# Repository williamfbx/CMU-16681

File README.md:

# MRSD Project I
Subject Name: MRSD Project I  
Subject Code: 16681-A  
Semester Taken: Spring 2025  
Instructor: John M. Dolan  
Grade: A  
Difficulty: 5/5

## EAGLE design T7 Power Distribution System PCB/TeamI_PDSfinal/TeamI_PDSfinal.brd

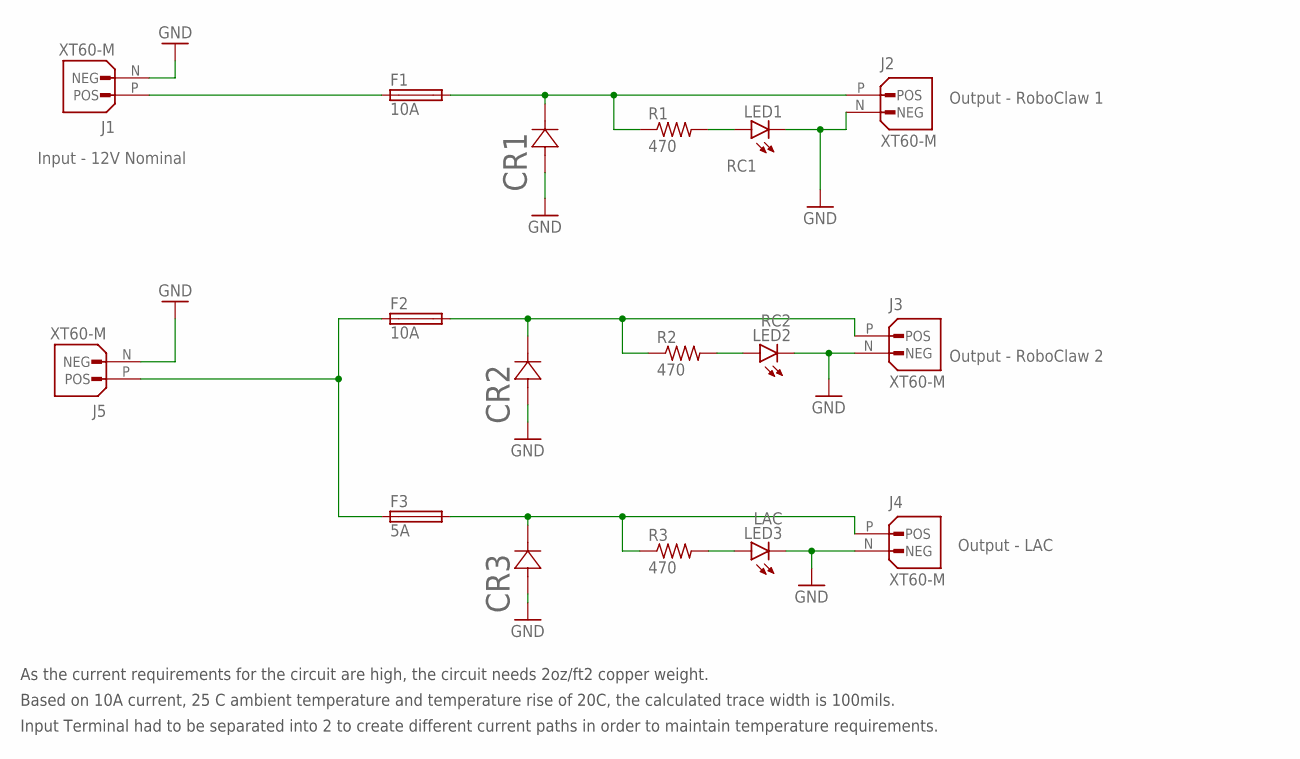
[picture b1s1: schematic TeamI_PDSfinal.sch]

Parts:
CR1, CR2, CR3: P4SMA16A; P4SMASERIES_LTF
F1, F2: 10A; TR5
F3: 5A; TE5
J1, J2, J3, J4, J5: XT60-M; AMASS_XT60-M
LED1: RC1; 1206
LED2: RC2; 1206
LED3: LAC; 1206
R1, R2, R3: 470; R1206

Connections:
GND: CR1.2, CR2.2, CR3.2, J1.N (NEG), J2.N (NEG), J3.N (NEG), J4.N (NEG), J5.N (NEG), LED1.C, LED2.C, LED3.C
unnamed: CR1.1, F1.2, J2.P (POS), R1.1
unnamed: CR3.1, F3.2, J4.P (POS), R3.1
unnamed: LED1.A, R1.2
unnamed: F1.1, J1.P (POS)
unnamed: CR2.1, F2.2, J3.P (POS), R2.1
unnamed: LED2.A, R2.2
unnamed: LED3.A, R3.2
unnamed: F2.1, F3.1, J5.P (POS)

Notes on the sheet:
Input - 12V Nominal
Output - RoboClaw 1
Output - RoboClaw 2
Output - LAC
As the current requirements for the circuit are high, the circuit needs 2oz/ft2 copper weight.
Based on 10A current, 25 C ambient temperature and temperature rise of 20C, the calculated trace width is 100mils.
Input Terminal had to be separated into 2 to create different current paths in order to maintain temperature requirements.

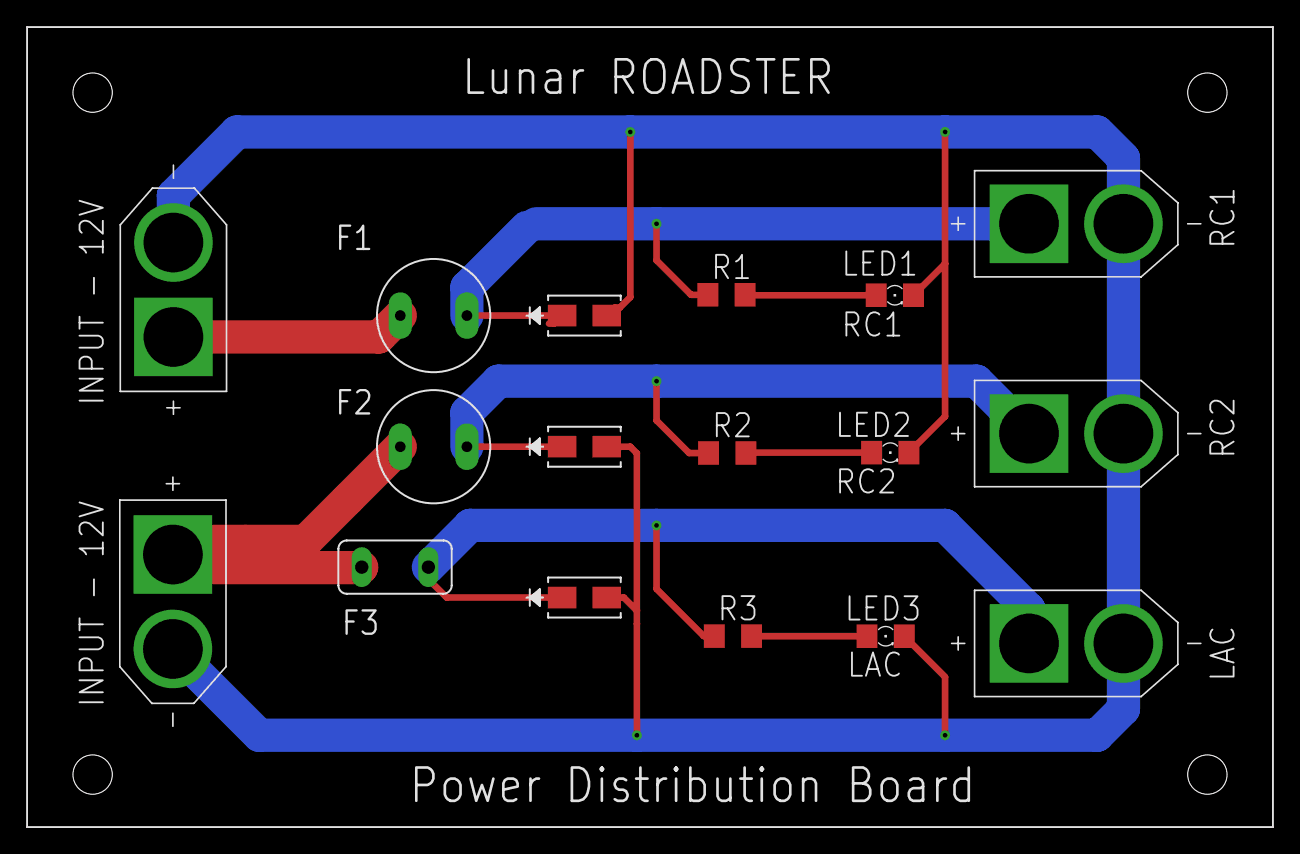
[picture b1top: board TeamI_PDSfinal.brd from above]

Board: 2 copper layers, 95.0 x 61.0 mm, 17 parts (0 on the bottom side), 9 nets.

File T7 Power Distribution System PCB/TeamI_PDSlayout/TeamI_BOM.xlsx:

Quantity | Value | Part Designator | Part Number | Vendor Link | Cost per part ($) | Package | Description
4 | P4SMA16A | CR1, CR2, CR3 | P4SMA16A | P4SMA16A | 0.43 | SMASERIES_LTF | Diode
6 | 10A | F1, F2 | TR5 - 37321000000 | 37321000000 | 1.29 | TE5 | Fuse
3 | 5A | F3 | TE5 - 39515000440 | 39515000440 | 1.57 | TE5 | Fuse
6 | XT60-M | J1, J2, J3, J4, J5 | XT60-M | XT60 | 0.89 | AMASS_XT60-M | Connector
5 | LEDSMT1206 | LED1, LED2, LED3 | 1206 SMD | 1206 SMD | 0.04 | 1206 | LED
5 | 470 Ω | R1, R2, R3 | CR1206-FX-4700ELF | CR1206-FX-4700ELF | 0.1 | R1206 | Resistor
 |  |  |  |  |  | 0

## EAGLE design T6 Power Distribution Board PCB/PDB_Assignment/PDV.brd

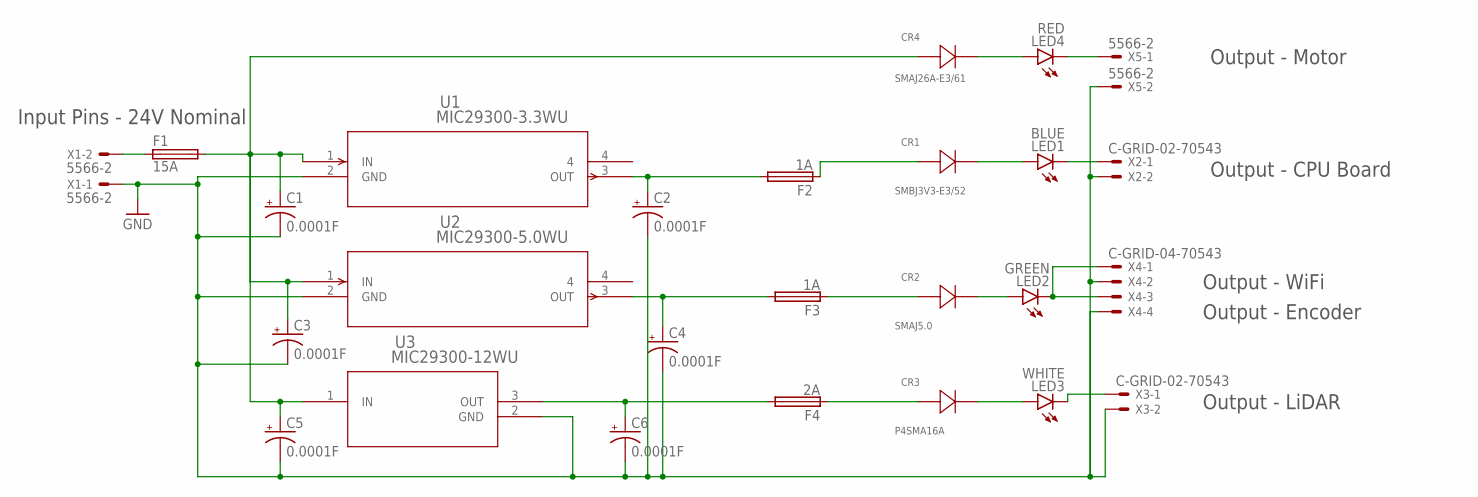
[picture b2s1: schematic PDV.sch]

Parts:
C1, C2, C3, C4, C5, C6: 0.0001F; E2,5-6
CR1: SMBJ3V3-E3/52; CR_V3-E3/52_VIS
CR2: SMAJ5.0; SMASERIES_LTF
CR3: P4SMA16A; P4SMASERIES_LTF
CR4: SMAJ26A-E3/61; DIODE_DO-214AC
F1: 15A; TE5
F2, F3: 1A; TE5
F4: 2A; TE5
LED1: BLUE; 1206
LED2: GREEN; 1206
LED3: WHITE; 1206
LED4: RED; 1206
U1: MIC29300-3.3WU; TO-263-3_MCL
U2: MIC29300-5.0WU; TO-263-3_MCL
U3: MIC29300-12WU; TO220-3LD-PL-1_MCH
X1, X5: 5566-2
X2, X3: C-GRID-02-70543; 70543-02
X4: C-GRID-04-70543; 70543-04

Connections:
GND: C1.-, C2.-, C3.-, C4.-, C5.-, C6.-, U1.2 (GND), U2.2 (GND), U3.2 (GND), X1.1, X2.2, X3.2, X4.2, X4.4, X5.2
unnamed: F1.1, X1.2
unnamed: C1.+, C3.+, C5.+, CR4.2, F1.2, U1.1 (IN), U2.1 (IN), U3.1 (IN)
unnamed: C2.+, F2.2, U1.3 (OUT)
unnamed: C4.+, F3.2, U2.3 (OUT)
unnamed: C6.+, F4.2, U3.3 (OUT)
unnamed: CR1.2, F2.1
unnamed: CR2.2, F3.1
unnamed: CR3.2, F4.1
unnamed: CR4.1, LED4.A
unnamed: LED4.C, X5.1
unnamed: CR1.1, LED1.A
unnamed: LED1.C, X2.1
unnamed: CR2.1, LED2.A
unnamed: LED2.C, X4.1, X4.3
unnamed: CR3.1, LED3.A
unnamed: LED3.C, X3.1

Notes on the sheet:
Input Pins - 24V Nominal
Output - Motor
Output - CPU Board
Output - WiFi
Output - Encoder
Output - LiDAR

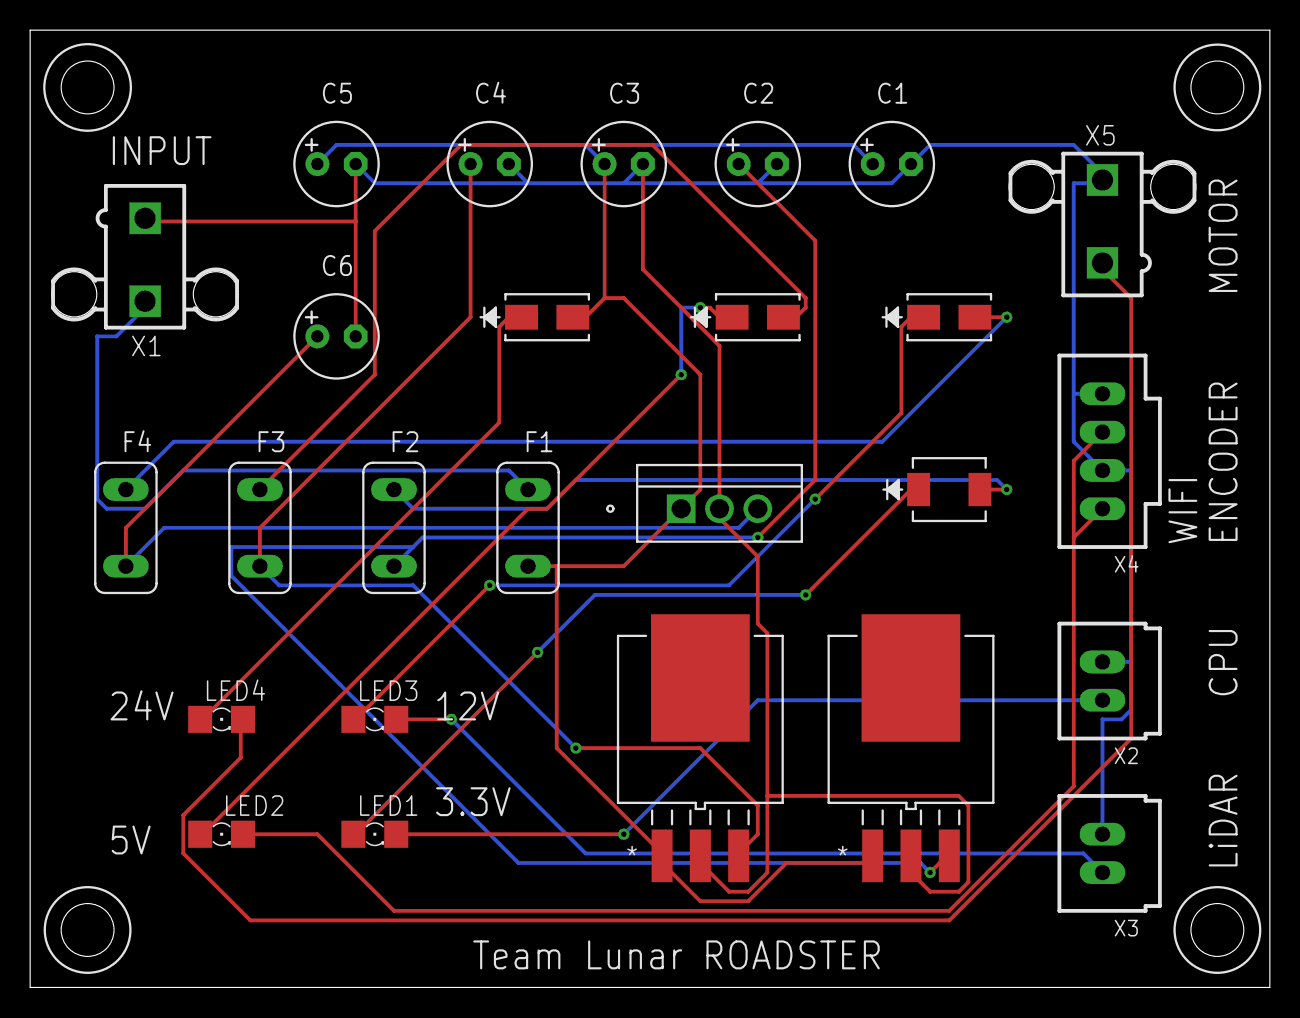
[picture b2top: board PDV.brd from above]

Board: 2 copper layers, 82.2 x 63.5 mm, 26 parts (0 on the bottom side), 17 nets.

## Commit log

2025-02-12 added Task 4
2025-02-12 Added Task 6
2025-02-14 Added Task 5
2025-02-19 Added Task 7
2025-02-25 Updated Task 8
2025-02-28 Added PR Slides
2025-02-28 Added Task 9 and Updated Task 7
2025-03-09 added task 11
2025-03-11 added task 10
2025-03-12 added task 12
2025-03-13 updated task 7
2025-03-15 updated task 10
2025-03-21 added T13
2025-04-10 added PR4
2025-04-17 added task 15
2025-04-25 added t16
2025-04-28 added task 17
2025-04-28 updated task 20
2025-04-28 updated task 11
2025-04-29 added task 19
2025-04-29 added task 21
2025-04-29 updated task 17
2025-05-03 added task 18

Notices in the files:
parts and their libraries:
COPYRIGHT: Copyright (C) 2025 Ultra Librarian. All rights reserved.
